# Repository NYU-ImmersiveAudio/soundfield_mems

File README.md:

# MEMS FOA Mic - ⌘

## Intro

This is a repository housing all things related to the slick new soundfield MEMS mic created in collaboration with NYU postdoc [Charlie Mydlarz](http://cusp.nyu.edu/people/charlie-mydlarz/) and graduate students from NYU's [MTech program](http://steinhardt.nyu.edu/music/technology). We are designing a first order ambisonics mic with an enclosure entirely 3D printed, hand soldered and reflowed electronics, and custom circuit boards designed in [Eagle](http://www.autodesk.com/products/eagle/overview). The boards can also be modified in [KiCad](http://kicad-pcb.org/) (an open source solution if anyone is looking for one).

We are making this project open source so that anyone who wants to experiment with ambisonics can print and build the mic themselves. The encoder will also be included and should run on [Matlab](https://www.mathworks.com/products/matlab) or [Octave GNU](https://www.gnu.org/software/octave). Let us know if there are any issue running on Octave, we have not tested this yet!

<!-- ## Materials
### Essential materials
- Soldering gun
  - The hotter the better. You really don't want to be stingy with this because having a soldering gun that takes a long time to melt your solder will be a pain in the a**.
- Solder
 - You will use this solder to connect the battery to the PCB and the cables from the microphone to adaptors that fit into your audio interface. Naturally you will also need some adaptors such as mini-XLRs or normal XLR adaptors.
You can use any audio interface that has 4 inputs.
Remember, keep phantom power off!
- Solder paste for MEMS microphone.
  - You will use this solder paste to [surface mount](https://mad-science.wonderhowto.com/how-to/make-surface-mount-electronics-home-for-smaller-cheaper-diy-gadgets-0135537/) the capsules to the PCB in the [reflow oven](https://mad-science.wonderhowto.com/how-to/diy-lab-equipment-build-your-own-reflow-oven-out-toaster-for-precision-temperature-soldering-0135536/).  
- 0.1μF surface mounted decoupling capacitor (one per capsules for a total of 4).
  - It's a good idea to get extras of everything in case something goes wrong. I believe these are the ones we used. I also believe since they are dielectric it does not matter which direction you mount them, but I'll have to ask Charlie.
- Analog MEMS capsules.
  - You can buy them [here](https://www.invensense.com/products/analog/ics-40720/).
  - Download the data sheet to get access to the heat profile.
  - You will need the profile in order to know how hot to run your oven.  
- Custom PCB boards.
  - Find the Eagle files on the repo.
  - We had ours manufactured with [OSH Park](https://blog.oshpark.com/).
- Cables to connect the boards to the breakout board.
  - We used non-braided to make soldering easier. Braided wires tend to be easier to bend which can be helpful but need to be tinned. Tinning is the process of adding a bit of solder to the end of a braided wire so it "behaves".
- A reflow oven
  - If you don't want to build your own you can generally find these at Universities or Engineering labs. Try also looking online to see if there are services that allow one to send parts to be surface mounted at a low price. Or try looking for tinkering stores/communities which might have one of these.
- 3V battery.
- The printed CAD model.
 - Again, you might be able to find a community around you that shares 3D printers.  
- Tweezers for placing components on the PCB.
  - Trust us, you want to get tweezers.

### Optional
- Multimeter: to check that none of your connections have short-circuited.
- A clamp to help with the soldering. -->

[Here](https://sites.google.com/nyu.edu/open-source-vr-mic-nyu/) is a link to our Google site with more info.

## Contributing

1. Fork it!
2. Create your feature branch: `git checkout -b my-new-feature`
3. Commit your changes: `git commit -m 'Add some feature'`
4. Push to the branch: `git push origin my-new-feature`
5. Submit a pull request :D

## Credits

- [Charlie Mydlarz](http://cusp.nyu.edu/people/charlie-mydlarz/) : Eagle Board Design
- [Gabriel Zalles](https://gzalles.github.io): CAD Design
- [Spencer Cappiello](www.spencercappiello.com): misc.
- [Ian Anderson](): misc.

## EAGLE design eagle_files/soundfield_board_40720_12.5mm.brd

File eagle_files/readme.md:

this is where we keep all the eagle files the CM made, there are boards of various sizes for you to use. the cad model is designed with the 12.5mm board in mind, so if you're going to use the cad model we made you need to make sure you have the right board made as well.

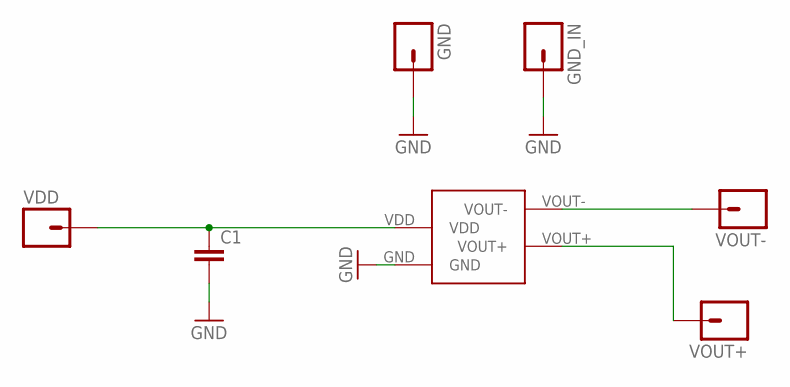
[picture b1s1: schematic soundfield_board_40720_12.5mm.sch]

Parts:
C1: 0.1UF-16V(+-10%)(0402); 0402-CAP
GND: M01PTH_NO_SILK_YES_STOP; 1X01_NO_SILK
GND_IN: M01PTH; 1X01
U$1: MEMS_ICS_40720
VDD: M01PTH; 1X01
VOUT+: M01PTH; 1X01
VOUT-: M01PTH; 1X01

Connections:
GND: C1.2, GND.1, GND_IN.1, U$1.GND
VDD: C1.1, U$1.VDD, VDD.1
VOUT+: U$1.VOUT+, VOUT+.1
VOUT-: U$1.VOUT-, VOUT-.1

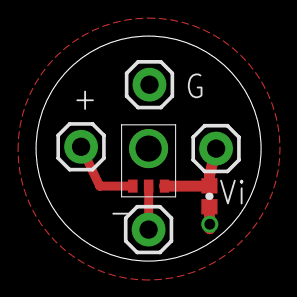
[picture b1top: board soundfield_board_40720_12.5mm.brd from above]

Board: 2 copper layers, 12.5 x 12.5 mm, 7 parts (0 on the bottom side), 4 nets.

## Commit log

2017-02-26 First commit with 15mm Invensense 40720 board using open hole wire terminations
2017-02-28 New read me file
    Mark down template for our project
2017-03-11 new cad design
    12.5 mm capsules
2017-03-14 I fixed the links
    The white space between the bracketed string and the link in parenthesis was causing an error not caught by markdown live preview. I fixed it.
2017-03-20 Fixed up the read me
    the whitespace between the [] and the links created an error
2017-03-27 Board updates
2017-05-25 Latest push
2017-06-01 New folder added for CAD
2017-06-05 Modified README
2017-07-24 ScanIR updates to handle auto measurement taking with placeholder function to trigger stepper motor with a given angle
2017-07-24 More commenting
2017-07-24 Comments
2017-07-25 First set of scripts for plotting polar response and frequency respsonse
2017-07-25 readme update
2017-07-25 stepper code
2017-11-22 Slight changes made to the README file
2017-11-22 added new cad files from MARKI
2017-11-22 added the mit license and added things to README
2017-11-22 Set theme jekyll-theme-minimal
2017-11-22 attempting to merge fork with remote
2017-11-22 added materials list to the readme
2017-12-04 removed unwanted cad files
2017-12-19 New code changes to fix missing code issue
2018-03-01 few new readmes
2018-03-01 added ignore for data folder
2018-03-01 gitignore data/
2018-03-01 remove files from cache and update ignore files
2018-03-07 removing images from repo
2018-03-07 added readme to eagle_files
2018-05-19 Added emoji

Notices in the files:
parts and their libraries:
SparkFun-Capacitors: Licensing: Creative Commons ShareAlike 4.0 International - https://creativecommons.org/licenses/by-sa/4.0
